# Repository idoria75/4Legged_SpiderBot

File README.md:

# 4Legged_SpiderBot
Version control of a quadruped robot utilizing Inverse Kinematics.
More info can be found on the docs folder.

*Please consider the circuits included in the docs folder instead of the ones found in the reports*

Current development on branch: hotfix.

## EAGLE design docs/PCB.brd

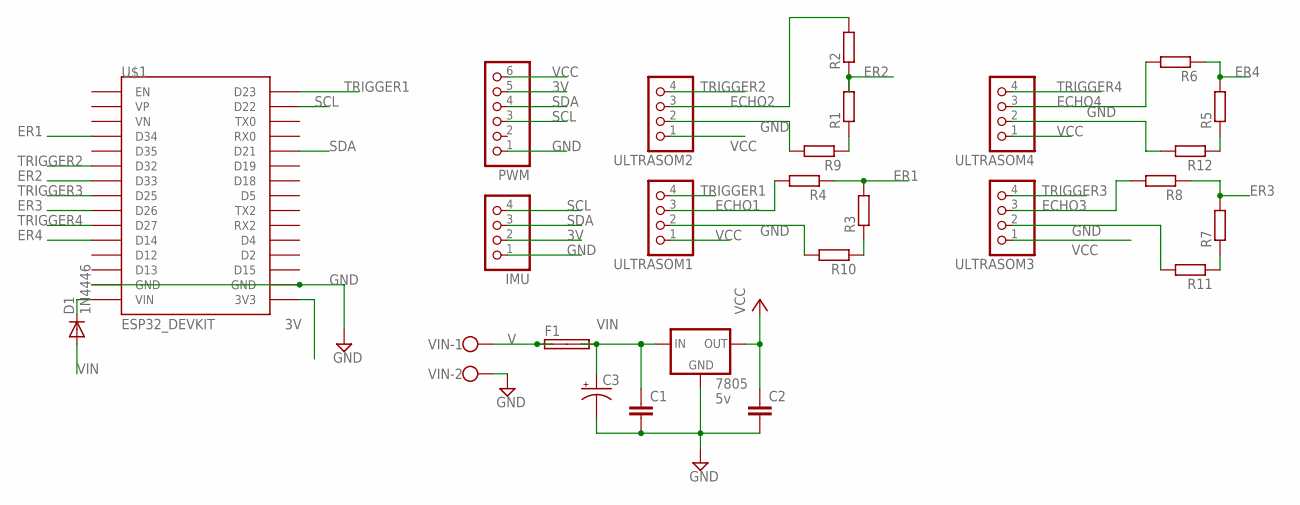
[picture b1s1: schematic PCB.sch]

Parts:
7805: 5v; 78MXXS
C1, C2: C-EU025-024X044; C025-024X044
C3: CPOL-USE2-5; E2-5
D1: 1N4446; DO35-10
F1: SHK20L
IMU: PINHD-1X4; 1X04
PWM: PINHD-1X6; 1X06
R1, R2, R3, R4, R5, R6, R7, R8, R9, R10, R11, R12: R-EU_0207/7; 0207/7
U$1: ESP32_DEVKIT
ULTRASOM1, ULTRASOM2, ULTRASOM3, ULTRASOM4: PINHD-1X4; 1X04
VIN: W237-102

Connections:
3V: IMU.2, PWM.5, U$1.3V3
ECHO1: R4.2, ULTRASOM1.3
ECHO2: R2.2, ULTRASOM2.3
ECHO3: R8.2, ULTRASOM3.3
ECHO4: R6.2, ULTRASOM4.3
ER1: R3.2, R4.1, U$1.D34
ER2: R1.2, R2.1, U$1.D33
ER3: R7.2, R8.1, U$1.D26
ER4: R5.2, R6.1, U$1.D14
GND: 7805.GND, C1.2, C2.2, C3.-, IMU.1, PWM.1, R9.2, R10.2, R11.2, R12.2, U$1.GND@1 (GND), U$1.GND@2 (GND), ULTRASOM1.2, ULTRASOM2.2, ULTRASOM3.2, ULTRASOM4.2, VIN.2
unnamed: D1.C, U$1.VIN
unnamed: R5.1, R12.1
unnamed: R7.1, R11.1
unnamed: R3.1, R10.1
unnamed: R1.1, R9.1
SCL: IMU.4, PWM.3, U$1.D22
SDA: IMU.3, PWM.4, U$1.D21
TRIGGER1: U$1.D23, ULTRASOM1.4
TRIGGER2: U$1.D32, ULTRASOM2.4
TRIGGER3: U$1.D25, ULTRASOM3.4
TRIGGER4: U$1.D27, ULTRASOM4.4
V: F1.1A, F1.1B, VIN.1
VCC: 7805.OUT, C2.1, PWM.6, ULTRASOM1.1, ULTRASOM2.1, ULTRASOM3.1, ULTRASOM4.1
VIN: 7805.IN, C1.1, C3.+, D1.A, F1.2A, F1.2B

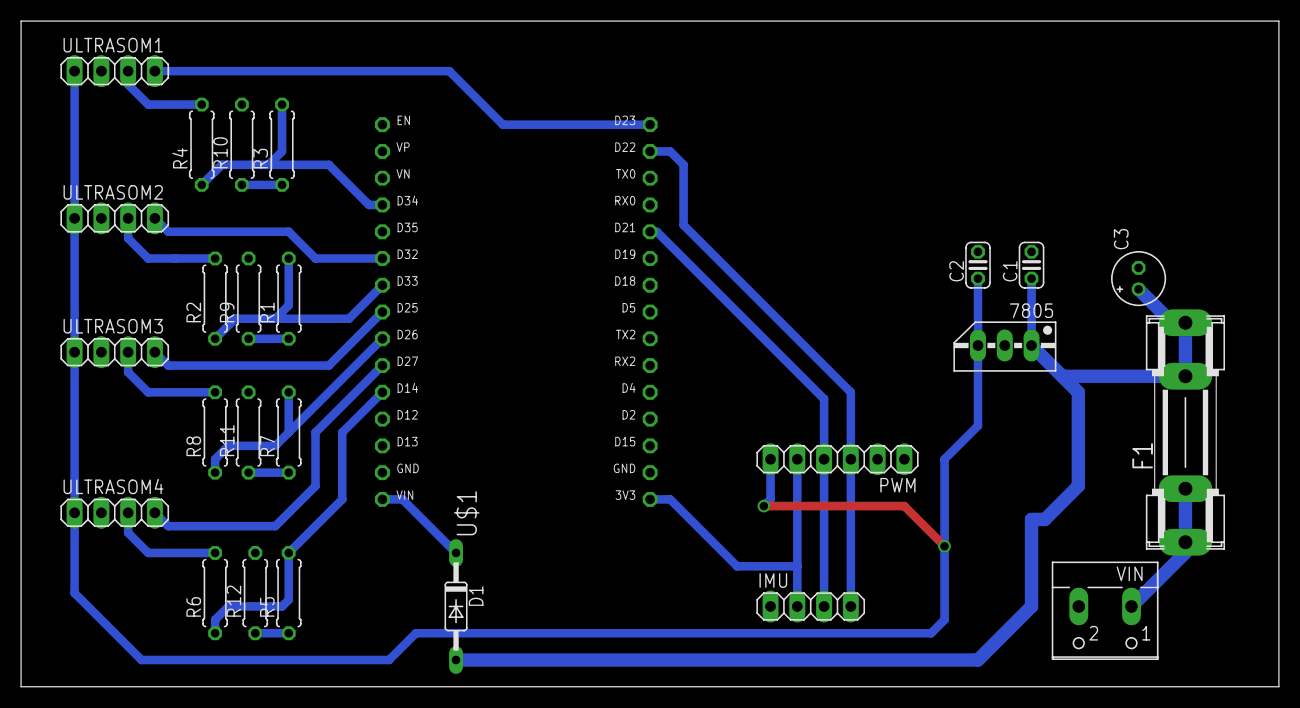
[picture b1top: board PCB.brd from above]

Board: 2 copper layers, 119.4 x 63.2 mm, 26 parts (0 on the bottom side), 24 nets.

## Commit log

2018-08-28 Changes to README.md
2018-09-18 Plot robot configuration
2018-09-18 Start moviment
    Desenvolvendo pirmieros movimentos
2018-09-18 Fixing kinemactic
2018-09-18 Add sequences
    Sequencia de movimentos para dar um passo
2018-09-20 V-REP
    Cenario V-REP para simulação
2018-09-22 V-REP robot
    Melhoria na montagem e apresentação de juntas e elos
2018-09-25 Robot V-REP
    Melhora na apresentação do robo via simulação para V-REP
2018-09-26 First version (not working) of comm. between python script and .ino
2018-09-27 Local socket via TCP
2018-09-30 V-REP
    FIxado qual elemento é responsável pela movimentação
2018-10-02 Vrep with python
    Simulation parameters fixed and first python codes
2018-10-02 Nothing is working
2018-10-02 Implement UDP Socket in Python
2018-10-02 Add IP
2018-10-02 Fix server and client scripts to listen from ESP
2018-10-02 Listen from TCP
2018-10-02 Organize TCP and UDP
2018-10-02 Start working on UDP communication
2018-10-02 V-REP Scenario
    Model the dummy points to generate de IK
2018-10-08 Add working example of the WebSocket implementation, will move on based on it
2018-10-08 Set ESP32 as AP (Router)
2018-10-08 Add comments
2018-10-08 Example of pthread use
2018-10-08 Example with Threads.h
2018-10-08 Add 2nd thread to blink LED
2018-10-08 Removes Network
2018-10-09 Add Thread file
2018-10-09 Switch to WebSocket branch with Thread
2018-10-09 Base code with AP and Blink Thread
2018-10-09 First working version os WebSocket Thread, needs more testing.
2018-10-15 Base structure of Switch Case for FSM
2018-10-15 Blinking FSM
2018-10-15 Movimentation FSM with LEDs
2018-10-16 Some code on classes
2018-10-16 Class Leg working
2018-10-16 Spider simulation is walking
2018-10-17 Change directory structure
2018-10-19 Ajust Parameters
    Ajust torque and mass based on real values
2018-10-23 Basic operation of servos
2018-10-23 Make spider keep standing up
2018-10-26 Update gitignore
2018-10-26 Fix vscode imports
2018-10-27 Moving code to header file definitions.h
2018-10-27 Finished moving code to header files, fix websockets code to keep track of number of messages received
2018-10-27 Add servotest code
2018-10-28 First version of JSON implementation
2018-10-29 JSON Communication working via WS
2018-10-29 Updates to work with JSON based on changes made on branch "Network"
2018-10-29 Modify JSON structure to comply with the one made by seashell
2018-10-29 Finish first version of JSON Communication
2018-10-29 Code Refactor
2018-10-30 Add Pinouts
2018-11-01 Finish reading sensor, update JSON based on distance w/o MUTEX
2018-11-05 Modify constructors
2018-11-05 Fix constructors, update methods
2018-11-05 New method to write to servos
2018-11-05 Define robot as global
2018-11-07 Small code refactor
2018-11-07 Leg constructors without initial angle definition
2018-11-07 File reorganization
2018-11-12 Fix Constructor for Robot
2018-11-12 Add Sensor files and update sensor pins
2018-11-13 Create class USensor and add method to get distance
2018-11-13 Move sensors to Robot
2018-11-13 USENSOR TEST
2018-11-13 Finish sensor implementation
2018-11-13 Code refactor and add serializeLegs()
2018-11-13 Move to new FSM implementation, code refactor, remove unnecessary funcs
2018-11-15 Move servo code to leg and make servoDriver static and part of the Leg
2018-11-16 Remove message that caused errors
2018-11-16 Add function to change stance and fix communication problems
2018-11-17 Update constructors (verified), add OTA (to test)
2018-11-17 Add base code for OTA
2018-11-17 Add makefile, fix OTA IP
2018-11-17 Fix espota.py based on latest version
2018-11-17 Small fixes to data types
2018-11-20 Implement basic movements on servos
2018-11-22 Add bootloader pinout img
2018-11-22 First working version of states via fsm library
2018-11-23 parameters to move the robot
2018-11-24 Check working sensors
2018-11-24 Fix sensorData write do json
2018-11-24 add change base function
2018-12-06 try to fix problems with WS and I2C
2019-02-08 remove some prints
2019-02-08 Add quadpod-ui
2019-03-15 Fix pin assignment
2019-03-21 Add PCB files
2019-03-21 Add reports and other files to docs
2020-05-03 Remove quadpod-ui due to security issues
